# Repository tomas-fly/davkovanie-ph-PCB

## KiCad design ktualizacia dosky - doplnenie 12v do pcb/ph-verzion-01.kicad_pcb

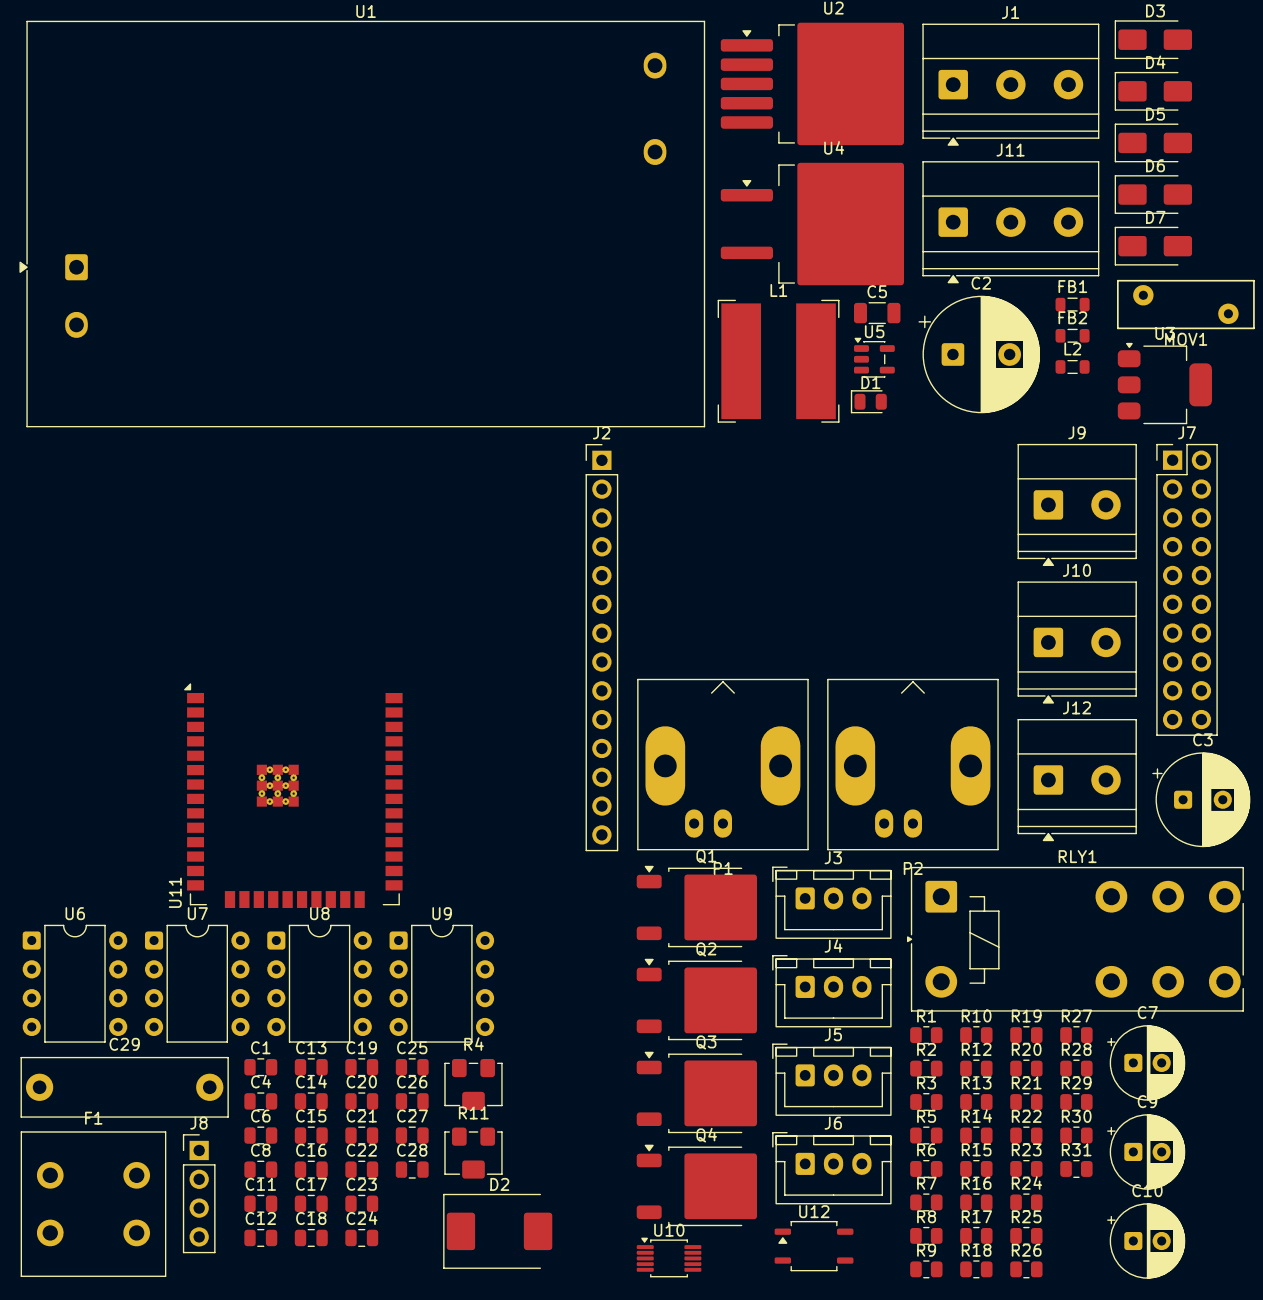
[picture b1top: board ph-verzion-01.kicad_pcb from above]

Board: 2 copper layers, 104 parts (0 on the bottom side), 71 nets, no tracks yet.

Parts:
C1, C6, C8, C15, C16, C17, C18, C21, C22, C23, C24, C25, C26, C28: 100nF; C_0805_2012Metric
C2: 680uF/25V; CP_Radial_D10.0mm_P5.00mm
C3: 220uF/10V; CP_Radial_D8.0mm_P3.50mm
C4, C12, C27: 10uF; C_0805_2012Metric
C5: 22uF; C_1206_3216Metric
C7: 10uF/25V; CP_Radial_D6.3mm_P2.50mm
C9: 10uF/16V; CP_Radial_D6.3mm_P2.50mm
C10: 47uF/16V; CP_Radial_D6.3mm_P2.50mm
C11, C14, C20: 1uF; C_0805_2012Metric
C13, C19: 2.2nF; C_0805_2012Metric
C29: 100nF_X2; C_Rect_L18.0mm_W5.0mm_P15.00mm_FKS3_FKP3
D1: Blue; LED_0805_2012Metric
D2: SS34; D_SMC
D3, D4, D5, D6: SS14; D_SMA
D7: M7; D_SMA
F1: 2A/250V; Fuseholder_Cylinder-5x20mm_Schurter_FPG4_Vertical_Closed
FB1, FB2: 600R@100MHz; L_0805_2012Metric
J1: 230V_IN; TerminalBlock_Phoenix_MKDS-1,5-3-5.08_1x03_P5.08mm_Horizont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
J2: DISPLAY; PinHeader_1x14_P2.54mm_Vertical
J3: 1W_1; JST_XH_B3B-XH-A_1x03_P2.50mm_Vertical
J4: 1W_2; JST_XH_B3B-XH-A_1x03_P2.50mm_Vertical
J5: 1W_3; JST_XH_B3B-XH-A_1x03_P2.50mm_Vertical
J6: 1W_4; JST_XH_B3B-XH-A_1x03_P2.50mm_Vertical
J7: GPIO_EXT; PinHeader_2x10_P2.54mm_Vertical
J8: UART; PinHeader_1x04_P2.54mm_Vertical
J9: OUT3; TerminalBlock_Phoenix_MKDS-1,5-2-5.08_1x02_P5.08mm_Horizont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
J10: OUT4; TerminalBlock_Phoenix_MKDS-1,5-2-5.08_1x02_P5.08mm_Horizont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
J11: AC_OUT_230V; TerminalBlock_Phoenix_MKDS-1,5-3-5.08_1x03_P5.08mm_Horizont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
J12: 12V_IO; TerminalBlock_Phoenix_MKDS-1,5-2-5.08_1x02_P5.08mm_Horizont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
L1: 33uH; L_Bourns-SRN1060
L2: 10uH; L_0805_2012Metric
MOV1: 275V; RV_Disc_D12mm_W4.2mm_P7.5mm
P1: pH_BNC; BNC_Amphenol_B6252HB-NPP3G-50_Horizontal
P2: ORP_BNC; BNC_Amphenol_B6252HB-NPP3G-50_Horizontal
Q1, Q2, Q3, Q4: IRLR2905; TO-252-2
R1, R5, R12, R29: 1k; R_0805_2012Metric
R2, R9: 4.7M; R_0805_2012Metric
R3, R10: 2.2k; R_0805_2012Metric
R4, R11: 5k; Potentiometer_Bourns_3214W_Vertical
R6, R7, R13, R14: 30k; R_0805_2012Metric
R8, R15: 75k; R_0805_2012Metric
R16, R17, R31: 4.7k; R_0805_2012Metric
R18, R19, R24, R25, R26, R27: 10k; R_0805_2012Metric
R20, R21, R22, R23, R30: 100R; R_0805_2012Metric
R28: 330R; R_0805_2012Metric
RLY1: Finder_40.52; Relay_DPDT_Finder_40.52
U1: HLK-30M12; Converter_ACDC_Hi-Link_HLK-30Mxx
U2: LM2596S-5.0; TO-263-5_TabPin3
U3: LD1117AS33TR; SOT-223-3_TabPin2
U4: L7805ABD2T; TO-263-2
U5: TPS60400; SOT-23-5
U6, U8: CA3140EZ; DIP-8_W7.62mm
U7, U9: TL071IP; DIP-8_W7.62mm
U10: ADS1115; MSOP-10_3x3mm_P0.5mm
U11: ESP32-WROOM-32E-N4; ESP32-WROOM-32E
U12: LTV-356T; SOP-4_3.8x4.1mm_P2.54mm

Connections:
+3V3: C5.1, C25.1, C26.1, C27.1, J2.1, J3.1, J4.1, J5.1, J6.1, J7.15, J8.1, R16.1, R17.1, R18.1, R19.1, R31.1, U3.2 (VOUT), U10.8 (VDD), U11.2 (3V3)
+5V: C3.1, C4.1, J7.16, L1.2, U2.4 (FB), U3.3 (VIN)
+5V_AN: C15.1, C17.1, C21.1, C23.1, FB1.2, U5.1 (IN), U6.7 (V+), U7.7 (V+), U8.7 (V+), U9.7 (V+)
+12V: C1.1, C2.1, C6.1, C7.1, D3.1 (K), D3.2 (A), D4.2 (A), D5.1 (K), D5.2 (A), D6.1 (K), D6.2 (A), D7.2 (A), J7.17, J9.1, J9.2, J10.1, J10.2, J12.1, Q1.2 (D), Q3.2 (D), Q4.2 (D), R1.1, R29.1, RLY1.A1 (COIL+), U1.3 (+12V), U2.1 (VIN), U4.1 (IN)
-5V_AN: C16.1, C18.1, C22.1, C24.1, FB2.2, U6.4 (V-), U7.4 (V-), U8.4 (V-), U9.4 (V-)
/AC_L: C29.2, F1.1, J1.1, MOV1.2, RLY1.14 (NO1)
/AC_N: J1.2, J11.2, U1.2 (AC_N)
/GPIO12: J7.1, U11.14 (IO12)
/GPIO16: J7.3, U11.27 (IO16)
/GPIO17: J7.5, U11.28 (IO17)
/GPIO22: J7.7, U11.36 (IO22)
/GPIO34: J7.9, U11.6 (IO34)
/GPIO35: J7.11, U11.7 (IO35)
/GPIO36: J7.13, U11.4 (SVP/IO36)
/L_OUT: J11.1, MOV1.1, R30.1, RLY1.11 (COM)
/MOSFET1_GATE: R20.1, U11.9 (IO33)
/MOSFET2_GATE: R21.1, R29.2, U12.4 (C)
/MOSFET3_GATE: R22.1, U11.16 (IO13)
/MOSFET4_GATE: R23.1, U11.13 (IO14)
/ONEWIRE_DATA: J3.2, J4.2, J5.2, J6.2, R31.2, U11.29 (IO5)
/ORP_OUT: R13.2, U9.6 (OUT), U10.5 (AIN1)
/PE: J1.3, J11.3
/RELAY_CTRL: R28.1, U11.10 (IO25)
/SCL: R17.2, U10.10 (SCL), U11.12 (IO27)
/SDA: R16.2, U10.9 (SDA), U11.11 (IO26)
/SPI_MISO: J2.9, J2.13, U11.31 (IO19)
/SPI_MOSI: J2.6, J2.12, U11.37 (IO23)
/SPI_SCK: J2.7, J2.10, U11.30 (IO18)
/TFT_BL: J2.8, U11.8 (IO32)
/TFT_CS: J2.3, U11.23 (IO15)
/TFT_DC: J2.5, U11.24 (IO2)
/TFT_RST: J2.4, U11.26 (IO4)
/TOUCH_CS: J2.11, U11.33 (IO21)
/TOUCH_IRQ: J2.14, U11.5 (SVN/IO39)
/UART_RX: J8.3, U11.34 (IO3/RX)
/UART_TX: J8.2, U11.35 (IO1/TX)
/pH_OUT: R6.2, U7.6 (OUT), U10.4 (AIN0)
GND: C1.2, C2.2, C3.2, C4.2, C5.2, C6.2, C7.2, C8.2, C9.2, C10.2, C12.2, C13.2, C15.2, C16.2, C17.2, C18.2, C19.2, C21.2, C22.2, C23.2, C24.2, C25.2, C26.2, C27.2, C28.2, D1.2 (A), D2.1 (K), J2.2, J3.3, J4.3, J5.3, J6.3, J7.2, J7.4, J7.6, J7.8, J7.10, J7.12, J7.14, J7.18, J7.19, J7.20, J8.4, J12.2, P1.2 (Shield), P2.2 (Shield), Q1.3 (S), Q2.3 (S), Q3.3 (S), Q4.3 (S), R5.2, R8.2, R12.2, R15.2, R24.2, R25.2, R26.2, R27.2, U1.6 (GND), U2.3 (GND), U2.5 (ON/OFF), U3.1 (GND), U4.2 (GND), U5.2 (GND), U10.1 (ADDR), U10.3 (GND), U11.1 (GND), U11.15 (GND), U11.38 (GND), U11.39 (GND_PAD), U12.2 (K), U12.3 (E)
unnamed: C10.1, FB1.1, L2.2
unnamed: C29.1, R30.2
unnamed: D1.1 (K), R1.2
unnamed: D2.2 (A), L1.1, U2.2 (OUT)
unnamed: D4.1 (K), D7.1 (K), Q2.2 (D), RLY1.A2 (COIL-)
unnamed: P1.1 (Signal), R2.1
unnamed: P2.1 (Signal), R9.1
unnamed: Q1.1 (G), R20.2, R24.1
unnamed: Q2.1 (G), R21.2, R25.1
unnamed: Q3.1 (G), R22.2, R26.1
unnamed: Q4.1 (G), R23.2, R27.1
unnamed: R3.2, R4.1
unnamed: R4.3, R5.1
unnamed: R10.2, R11.1
unnamed: R11.3, R12.1
unnamed: F1.2, U1.1 (AC_L)
unnamed: C8.1, C9.1, L2.1, U4.3 (OUT)
unnamed: C11.1, U5.3 (C+)
unnamed: C11.2, U5.4 (C-)
unnamed: C12.1, FB2.1, U5.5 (OUT)
unnamed: C14.1, R3.1, U6.3 (IN+)
unnamed: C13.1, R2.2, U6.2 (IN-)
unnamed: C14.2, R7.1, U6.6 (OUT)
unnamed: R6.1, R7.2, U7.3 (IN+)
unnamed: R8.1, U7.2 (IN-)
unnamed: C20.1, R10.1, U8.3 (IN+)
unnamed: C19.1, R9.2, U8.2 (IN-)
unnamed: C20.2, R14.1, U8.6 (OUT)
unnamed: R13.1, R14.2, U9.3 (IN+)
unnamed: R15.1, U9.2 (IN-)
unnamed: C28.1, R18.2, U11.3 (EN)
unnamed: R19.2, U11.25 (IO0)
unnamed: R28.2, U12.1 (A)
